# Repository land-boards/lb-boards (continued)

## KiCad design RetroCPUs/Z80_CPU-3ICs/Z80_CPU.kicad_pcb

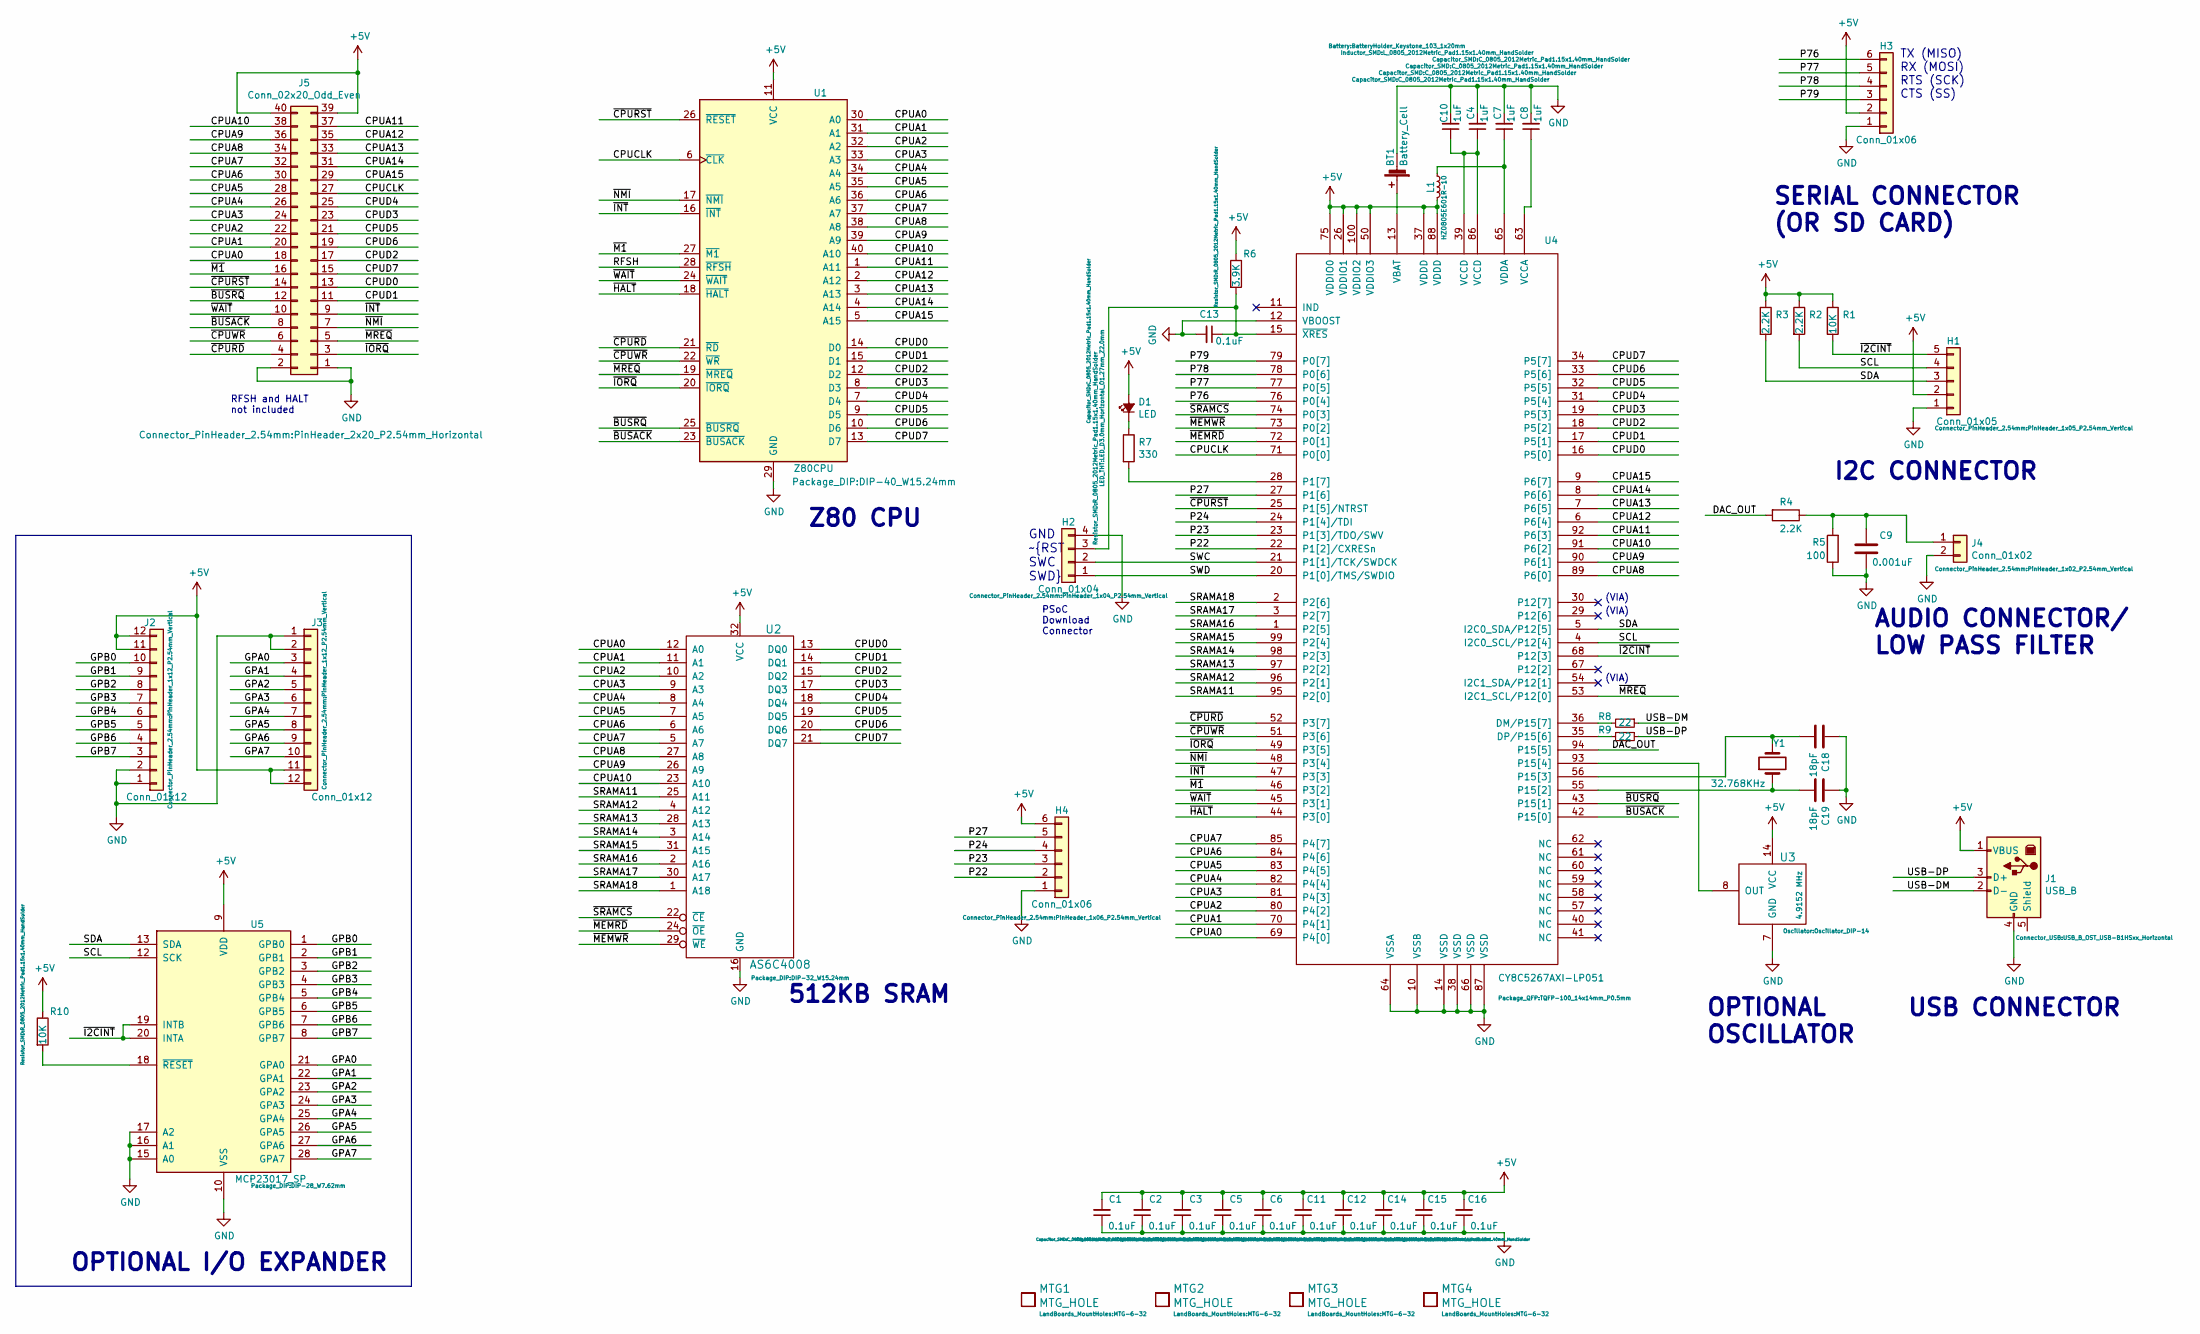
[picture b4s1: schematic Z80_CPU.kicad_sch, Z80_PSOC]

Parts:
BT1: Battery_Cell; BatteryHolder_Keystone_103_1x20mm
C1, C2, C3, C5, C6, C11, C12, C13, C14, C15, C16: 0.1uF; C_0805_2012Metric_Pad1.15x1.40mm_HandSolder
C4, C7, C8, C10: 1uF; C_0805_2012Metric_Pad1.15x1.40mm_HandSolder
C9: 0.001uF; C_0805_2012Metric_Pad1.15x1.40mm_HandSolder
C18, C19: 18pF; C_0805_2012Metric_Pad1.15x1.40mm_HandSolder
D1: LED; LED_D3.0mm_Horizontal_O1.27mm_Z2.0mm
H1: Conn_01x05; PinHeader_1x05_P2.54mm_Vertical
H2: Conn_01x04; PinHeader_1x04_P2.54mm_Vertical
H3, H4: Conn_01x06; PinHeader_1x06_P2.54mm_Vertical
J1: USB_B; USB_B_OST_USB-B1HSxx_Horizontal
J2, J3: Conn_01x12; PinHeader_1x12_P2.54mm_Vertical
J4: Conn_01x02; PinHeader_1x02_P2.54mm_Vertical
J5: Conn_02x20_Odd_Even; PinHeader_2x20_P2.54mm_Horizontal
L1: HZ0805E601R-10; L_0805_2012Metric_Pad1.15x1.40mm_HandSolder
MTG1, MTG2, MTG3, MTG4: MTG_HOLE; MTG-6-32
R1, R10: 10K; R_0805_2012Metric_Pad1.15x1.40mm_HandSolder
R2, R3, R4: 2.2K; R_0805_2012Metric_Pad1.15x1.40mm_HandSolder
R5: 100; R_0805_2012Metric_Pad1.15x1.40mm_HandSolder
R6: 3.9K; R_0805_2012Metric_Pad1.15x1.40mm_HandSolder
R7: 330; R_0805_2012Metric_Pad1.15x1.40mm_HandSolder
R8, R9: 22; R_0805_2012Metric_Pad1.15x1.40mm_HandSolder
U1: Z80CPU; DIP-40_W15.24mm
U2: AS6C4008; DIP-32_W15.24mm
U3: 4.9152 MHz; Oscillator_DIP-14
U4: CY8C5267AXI-LP051; TQFP-100_14x14mm_P0.5mm
U5: MCP23017_SP; DIP-28_W7.62mm
Y1: 32.768KHz; Crystal_C26-LF_D2.1mm_L6.5mm_Horizontal

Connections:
+5V: C1.2, C2.2, C3.2, C5.2, C6.2, C11.2, C12.2, C14.2, C15.2, C16.2, D1.2 (A), H1.2, H3.2, H4.6, J1.1 (VBUS), J2.11, J2.12, J3.11, J3.12, J5.39, J5.40, L1.2, R1.1, R2.1, R3.1, R6.1, R10.1, U1.11 (VCC), U2.32 (VCC), U3.14 (VCC), U4.26 (VDDIO1), U4.37 (VDDD), U4.50 (VDDIO3), U4.75 (VDDIO0), U4.88 (VDDD), U4.100 (VDDIO2), U5.9 (VDD)
/CPUA0: J5.18, U1.30 (A0), U2.12 (A0), U4.69 (P4[0])
/CPUA1: J5.20, U1.31 (A1), U2.11 (A1), U4.70 (P4[1])
/CPUA2: J5.22, U1.32 (A2), U2.10 (A2), U4.80 (P4[2])
/CPUA3: J5.24, U1.33 (A3), U2.9 (A3), U4.81 (P4[3])
/CPUA4: J5.26, U1.34 (A4), U2.8 (A4), U4.82 (P4[4])
/CPUA5: J5.28, U1.35 (A5), U2.7 (A5), U4.83 (P4[5])
/CPUA6: J5.30, U1.36 (A6), U2.6 (A6), U4.84 (P4[6])
/CPUA7: J5.32, U1.37 (A7), U2.5 (A7), U4.85 (P4[7])
/CPUA8: J5.34, U1.38 (A8), U2.27 (A8), U4.89 (P6[0])
/CPUA9: J5.36, U1.39 (A9), U2.26 (A9), U4.90 (P6[1])
/CPUA10: J5.38, U1.40 (A10), U2.23 (A10), U4.91 (P6[2])
/CPUA11: J5.37, U1.1 (A11), U4.92 (P6[3])
/CPUA12: J5.35, U1.2 (A12), U4.6 (P6[4])
/CPUA13: J5.33, U1.3 (A13), U4.7 (P6[5])
/CPUA14: J5.31, U1.4 (A14), U4.8 (P6[6])
/CPUA15: J5.29, U1.5 (A15), U4.9 (P6[7])
/CPUCLK: J5.27, U1.6 (~CLK), U4.71 (P0[0])
/CPUD0: J5.13, U1.14 (D0), U2.13 (DQ0), U4.16 (P5[0])
/CPUD1: J5.11, U1.15 (D1), U2.14 (DQ1), U4.17 (P5[1])
/CPUD2: J5.17, U1.12 (D2), U2.15 (DQ2), U4.18 (P5[2])
/CPUD3: J5.23, U1.8 (D3), U2.17 (DQ3), U4.19 (P5[3])
/CPUD4: J5.25, U1.7 (D4), U2.18 (DQ4), U4.31 (P5[4])
/CPUD5: J5.21, U1.9 (D5), U2.19 (DQ5), U4.32 (P5[5])
/CPUD6: J5.19, U1.10 (D6), U2.20 (DQ6), U4.33 (P5[6])
/CPUD7: J5.15, U1.13 (D7), U2.21 (DQ7), U4.34 (P5[7])
/DAC_OUT: R4.2, U4.94 (P15[5])
/GPA0: J3.3, U5.21 (GPA0)
/GPA1: J3.4, U5.22 (GPA1)
/GPA2: J3.5, U5.23 (GPA2)
/GPA3: J3.6, U5.24 (GPA3)
/GPA4: J3.7, U5.25 (GPA4)
/GPA5: J3.8, U5.26 (GPA5)
/GPA6: J3.9, U5.27 (GPA6)
/GPA7: J3.10, U5.28 (GPA7)
/GPB0: J2.10, U5.1 (GPB0)
/GPB1: J2.9, U5.2 (GPB1)
/GPB2: J2.8, U5.3 (GPB2)
/GPB3: J2.7, U5.4 (GPB3)
/GPB4: J2.6, U5.5 (GPB4)
/GPB5: J2.5, U5.6 (GPB5)
/GPB6: J2.4, U5.7 (GPB6)
/GPB7: J2.3, U5.8 (GPB7)
/P22: H4.2, U4.22 (P1[2]/CXRESn)
/P23: H4.3, U4.23 (P1[3]/TDO/SWV)
/P24: H4.4, U4.24 (P1[4]/TDI)
/P27: H4.5, U4.27 (P1[6])
/P76: H3.6, U4.76 (P0[4])
/P77: H3.5, U4.77 (P0[5])
/P78: H3.4, U4.78 (P0[6])
/P79: H3.3, U4.79 (P0[7])
/SCL: H1.4, R2.2, U4.4 (I2C0_SCL/P12[4]), U5.12 (SCK)
/SDA: H1.3, R3.2, U4.5 (I2C0_SDA/P12[5]), U5.13 (SDA)
/SRAMA11: U2.25 (A11), U4.95 (P2[0])
/SRAMA12: U2.4 (A12), U4.96 (P2[1])
/SRAMA13: U2.28 (A13), U4.97 (P2[2])
/SRAMA14: U2.3 (A14), U4.98 (P2[3])
/SRAMA15: U2.31 (A15), U4.99 (P2[4])
/SRAMA16: U2.2 (A16), U4.1 (P2[5])
/SRAMA17: U2.30 (A17), U4.3 (P2[7])
/SRAMA18: U2.1 (A18), U4.2 (P2[6])
/SWC: H2.2, U4.21 (P1[1]/TCK/SWDCK)
/SWD: H2.1, U4.20 (P1[0]/TMS/SWDIO)
/USB-DM: J1.2 (D-), R8.1
/USB-DP: J1.3 (D+), R9.1
/~BUSACK: J5.8, U1.23 (~BUSACK), U4.42 (P15[0])
/~BUSRQ: J5.12, U1.25 (~BUSRQ), U4.43 (P15[1])
/~CPURD: J5.4, U1.21 (~RD), U4.52 (P3[7])
/~CPURST: J5.14, U1.26 (~RESET), U4.25 (P1[5]/NTRST)
/~CPUWR: J5.6, U1.22 (~WR), U4.51 (P3[6])
/~HALT: U1.18 (~HALT), U4.44 (P3[0])
/~I2CINT: H1.5, R1.2, U4.68 (P12[3]), U5.19 (INTB), U5.20 (INTA)
/~INT: J5.9, U1.16 (~INT), U4.47 (P3[3])
/~IORQ: J5.3, U1.20 (~IORQ), U4.49 (P3[5])
/~M1: J5.16, U1.27 (~M1), U4.46 (P3[2])
/~MEMRD: U2.24 (~OE), U4.72 (P0[1])
/~MEMWR: U2.29 (~WE), U4.73 (P0[2])
/~MREQ: J5.5, U1.19 (~MREQ), U4.53 (I2C1_SCL/P12[0])
/~NMI: J5.7, U1.17 (~NMI), U4.48 (P3[4])
/~SRAMCS: U2.22 (~CE), U4.74 (P0[3])
/~WAIT: J5.10, U1.24 (~WAIT), U4.45 (P3[1])
GND: BT1.2 (-), C1.1, C2.1, C3.1, C4.2, C5.1, C6.1, C7.2, C8.2, C9.1, C10.2, C11.1, C12.1, C13.2, C14.1, C15.1, C16.1, C18.1, C19.1, H1.1, H2.4, H3.1, H4.1, J1.4 (GND), J2.1, J2.2, J3.1, J3.2, J4.2, J5.1, J5.2, R5.1, U1.29 (GND), U2.16 (GND), U3.7 (GND), U4.10 (VSSB), U4.12 (VBOOST), U4.14 (VSSD), U4.38 (VSSD), U4.64 (VSSA), U4.66 (VSSD), U4.87 (VSSD), U5.10 (VSS), U5.15 (A0), U5.16 (A1), U5.17 (A2)
unnamed: BT1.1 (+), U4.13 (VBAT)
unnamed: C7.1, L1.1, U4.65 (VDDA)
unnamed: C8.1, U4.63 (VCCA)
unnamed: C9.2, J4.1, R4.1, R5.2
unnamed: C4.1, C10.1, U4.39 (VCCD), U4.86 (VCCD)
unnamed: C13.1, H2.3, R6.2, U4.15 (~XRES)
unnamed: C18.2, U4.56 (P15[3]), Y1.2
unnamed: C19.2, U4.55 (P15[2]), Y1.1
unnamed: D1.1 (K), R7.1
unnamed: R7.2, U4.28 (P1[7])
unnamed: R8.2, U4.36 (DM/P15[7])
unnamed: R9.2, U4.35 (DP/P15[6])
unnamed: R10.2, U5.18 (~RESET)
unnamed: U3.8 (OUT), U4.93 (P15[4])

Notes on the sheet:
Z80 CPU
OPTIONAL I/O EXPANDER
(VIA)
OPTIONAL OSCILLATOR
AUDIO CONNECTOR/ LOW PASS FILTER
I2C CONNECTOR
SERIAL CONNECTOR (OR SD CARD)
USB CONNECTOR
512KB SRAM
PSoC Download Connector
TX (MISO) RX (MOSI) RTS (SCK) CTS (SS)
GND ~{RST SWC SWD}
RFSH and HALT not included

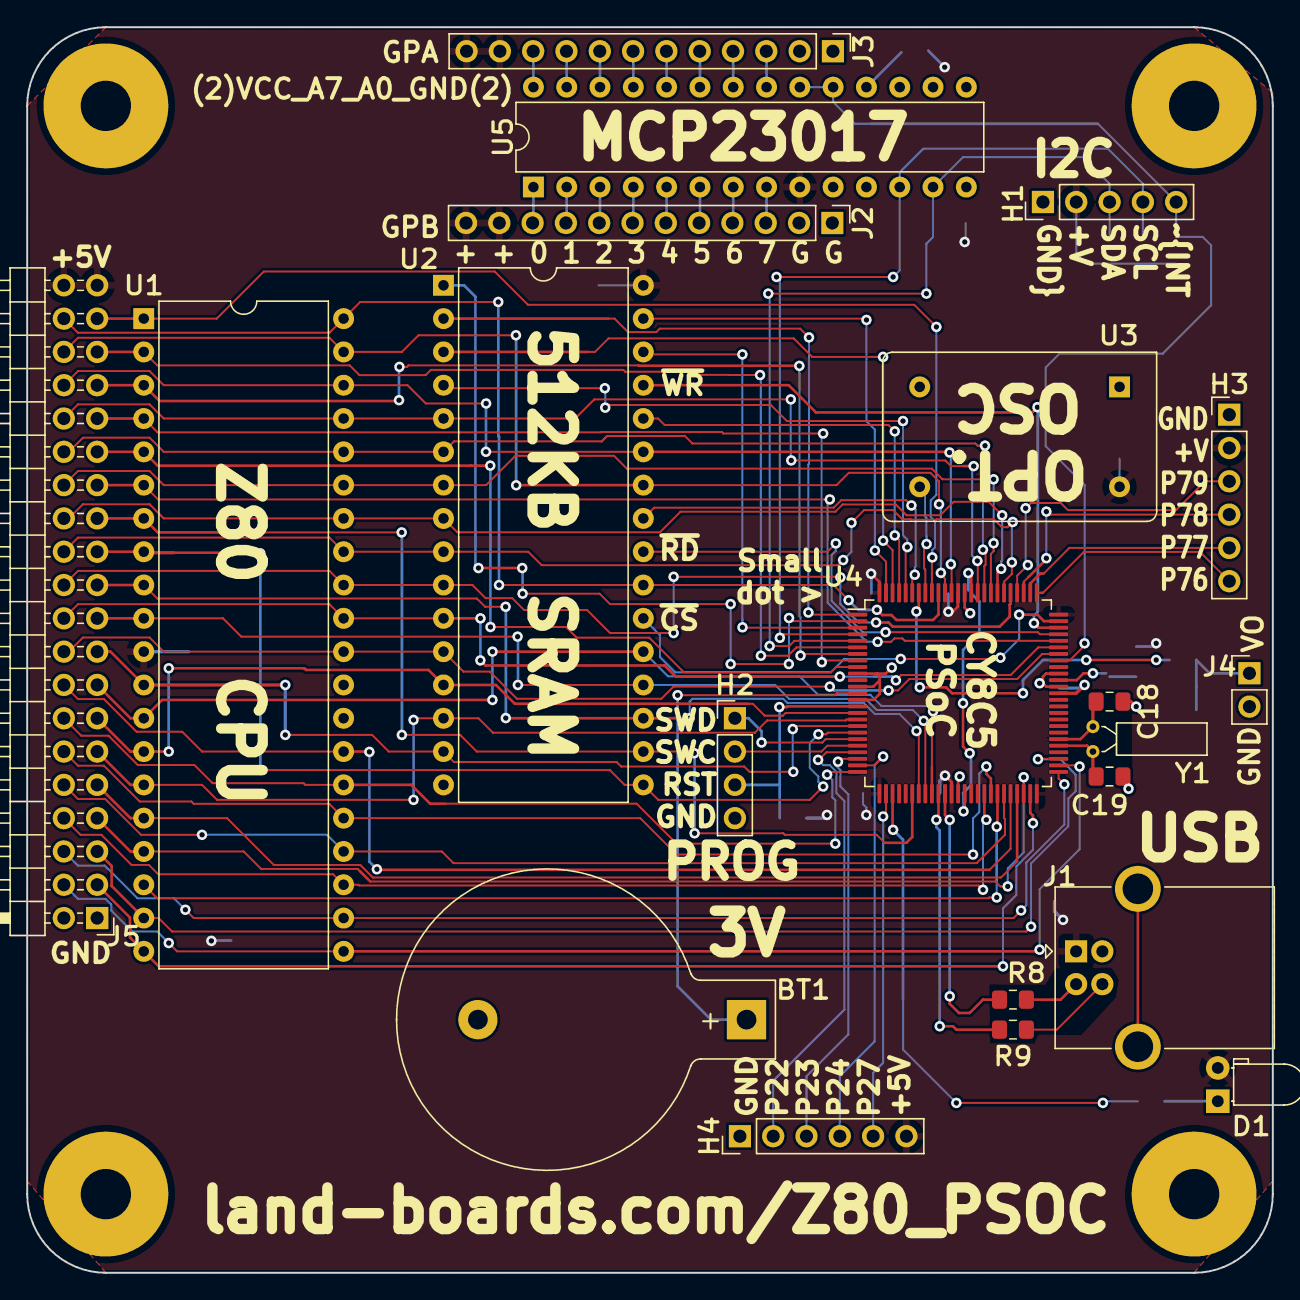
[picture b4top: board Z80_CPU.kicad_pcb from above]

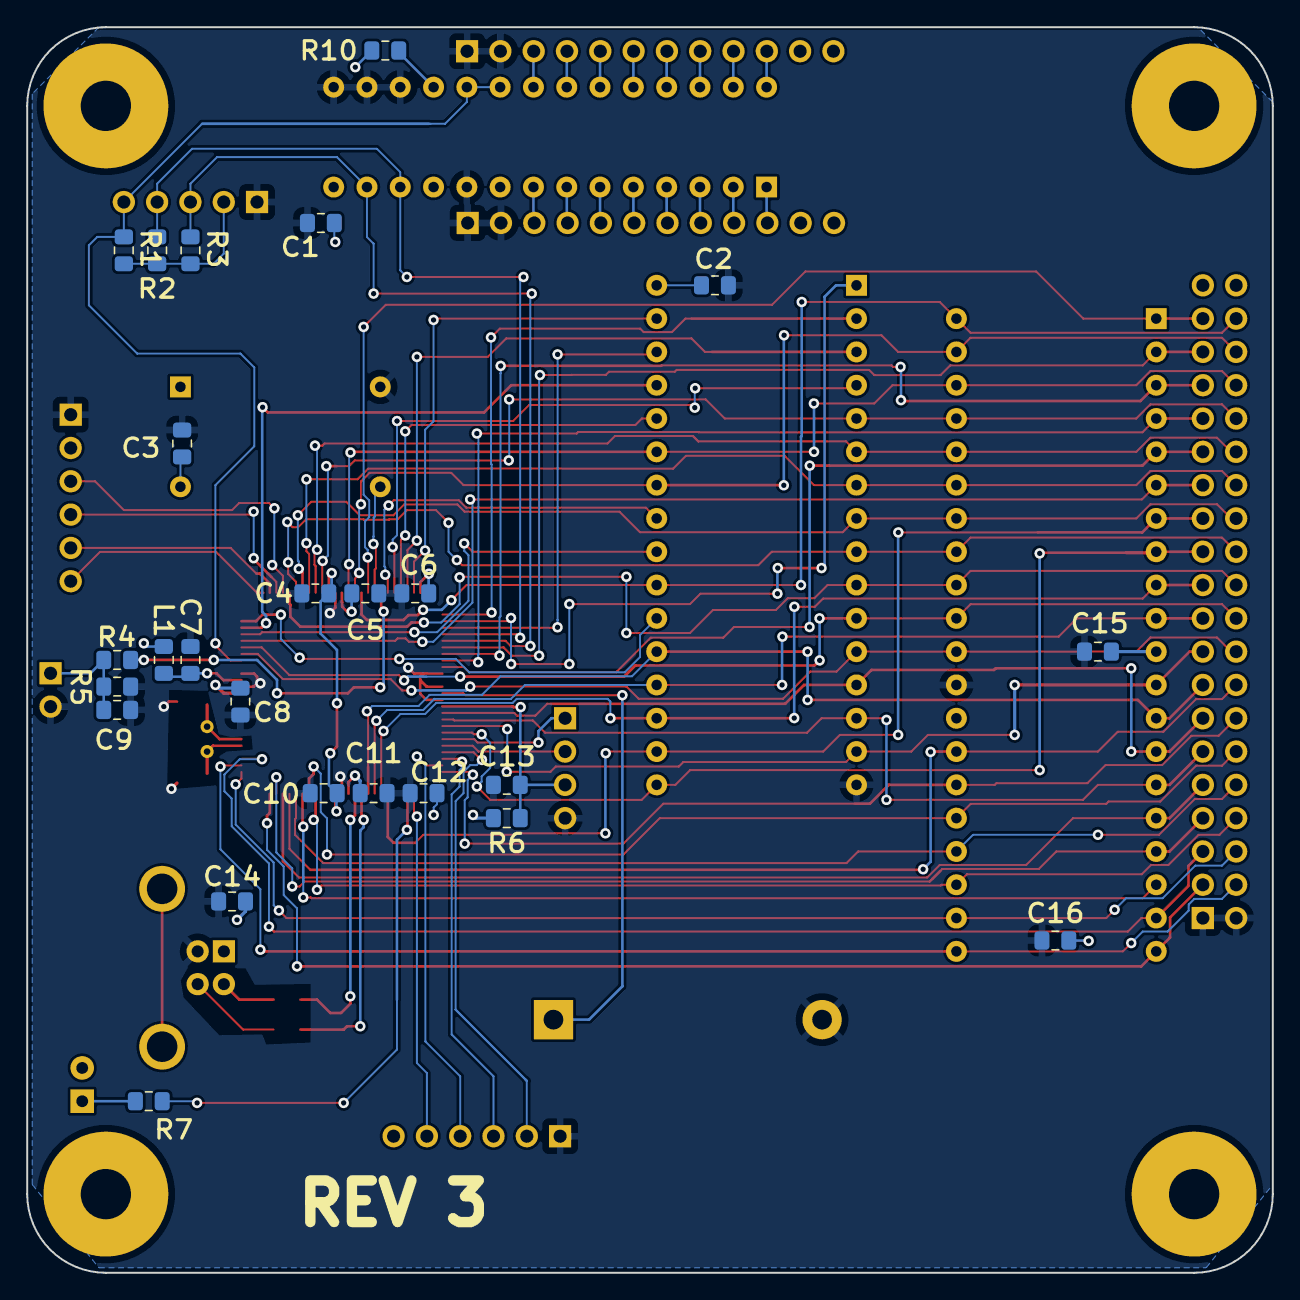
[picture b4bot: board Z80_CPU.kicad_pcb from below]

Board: 2 copper layers, 95.0 x 95.0 mm, 50 parts (25 on the bottom side), 96 nets.

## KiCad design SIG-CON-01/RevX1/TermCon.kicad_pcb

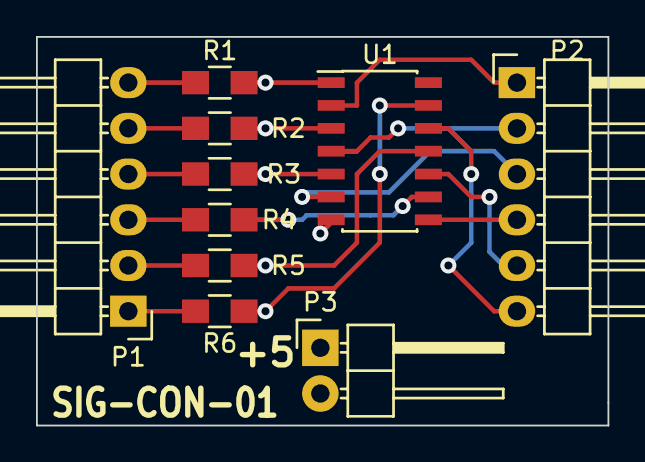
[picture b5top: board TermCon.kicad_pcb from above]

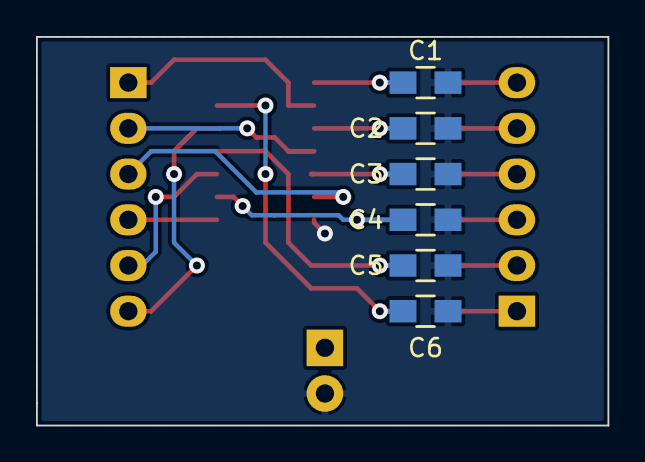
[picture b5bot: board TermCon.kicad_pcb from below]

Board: 2 copper layers, 31.8 x 21.6 mm, 16 parts (6 on the bottom side), 19 nets.

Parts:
C1, C2, C3, C4, C5, C6: C; C_0805_HandSoldering
P1, P2: CONN_01X06; Pin_Header_Angled_1x06
P3: CONN_01X02; Pin_Header_Angled_1x02
R1, R2, R3, R4, R5, R6: R; R_0805_HandSoldering
U1: 74AC14; SOIC-14_3.9x8.7mm_Pitch1.27mm

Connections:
GND: C1.2, C2.2, C3.2, C4.2, C5.2, C6.2, P3.2, U1.7
unnamed: C1.1, R1.1, U1.1
unnamed: C2.1, R2.1, U1.3
unnamed: C3.1, R3.1, U1.5
unnamed: C4.1, R4.1, U1.9
unnamed: C5.1, R5.1, U1.11
unnamed: C6.1, R6.1, U1.13
unnamed: P1.1, R6.2
unnamed: P1.2, R5.2
unnamed: P1.3, R4.2
unnamed: P1.4, R3.2
unnamed: P1.5, R2.2
unnamed: P1.6, R1.2
unnamed: P2.1, U1.2
unnamed: P2.2, U1.4
unnamed: P2.3, U1.6
unnamed: P2.4, U1.8
unnamed: P2.5, U1.10
unnamed: P2.6, U1.12

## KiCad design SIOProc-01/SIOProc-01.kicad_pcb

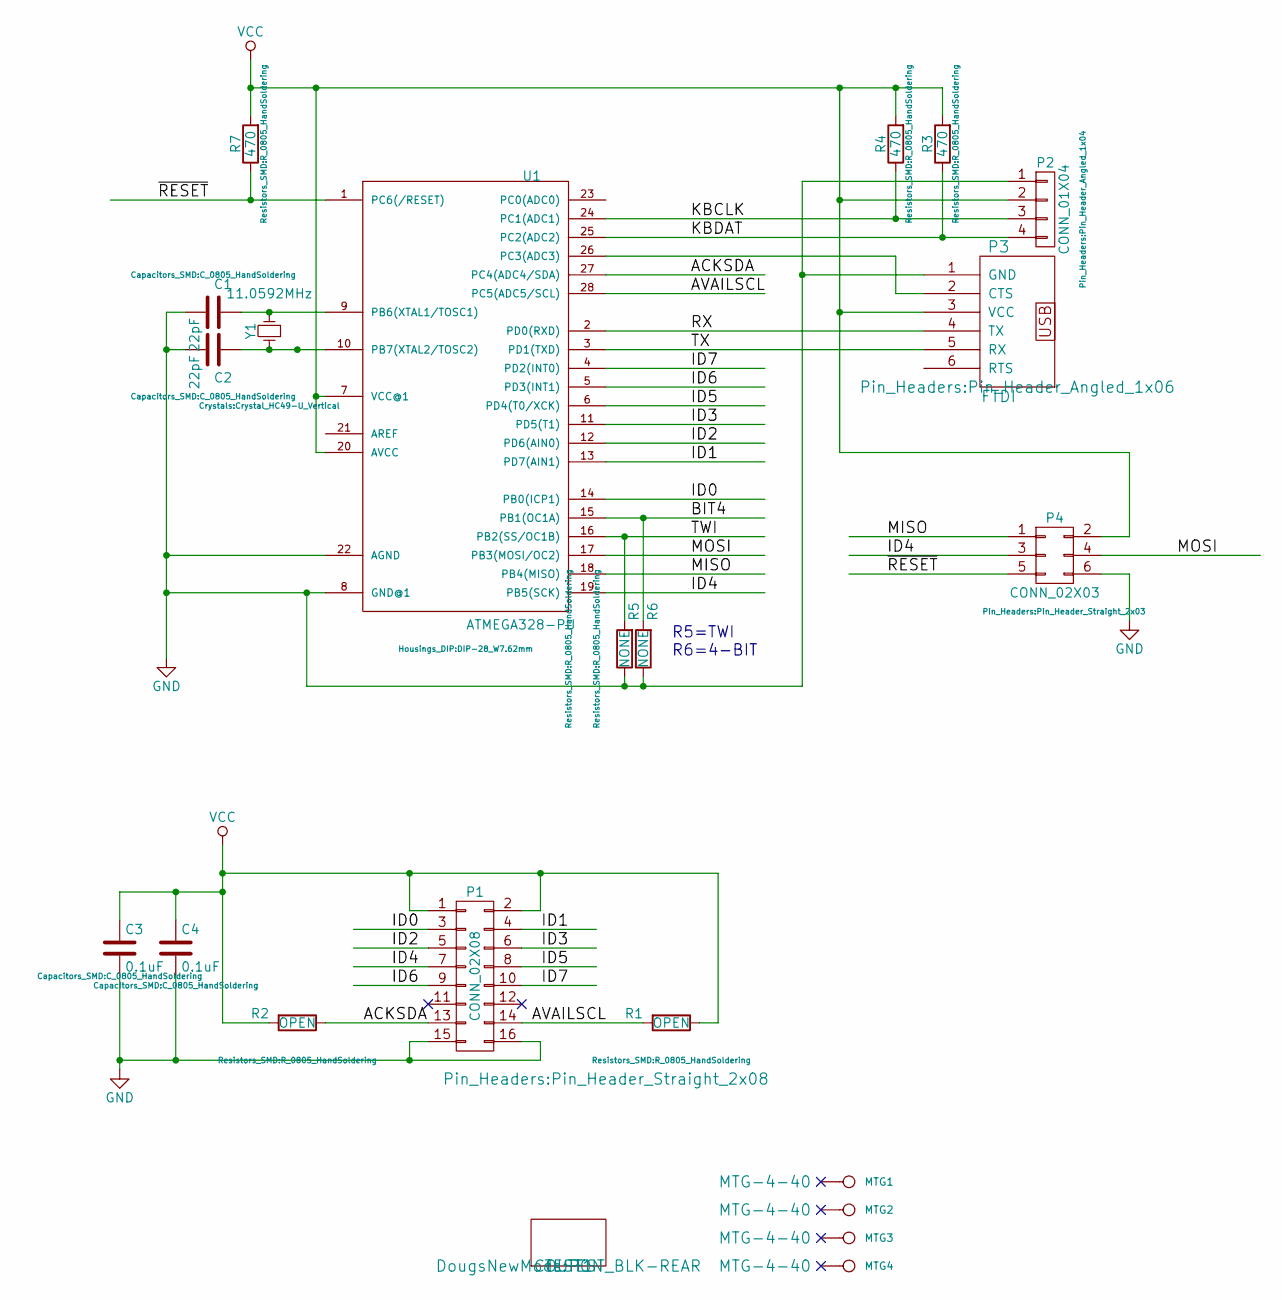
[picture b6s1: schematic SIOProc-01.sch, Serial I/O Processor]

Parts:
C1, C2: 22pF; C_0805_HandSoldering
C3, C4: 0.1uF; C_0805_HandSoldering
MTG1, MTG2, MTG3, MTG4: CONN_1; MTG-4-40
P1: CONN_02X08; Pin_Header_Straight_2x08
P2: CONN_01X04; Pin_Header_Angled_1x04
P3: FTDI; Pin_Header_Angled_1x06
P4: CONN_02X03; Pin_Header_Straight_2x03
R1, R2: OPEN; R_0805_HandSoldering
R3, R4, R7: 470; R_0805_HandSoldering
R5, R6: NONE; R_0805_HandSoldering
TEST1: COUPON; TEST_BLK-REAR
U1: ATMEGA328-PU; DIP-28_W7.62mm
Y1: 11.0592MHz; Crystal_HC49-U_Vertical

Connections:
/ACKSDA: P1.13, R2.1, U1.27 (PC4(ADC4/SDA))
/AVAILSCL: P1.14, R1.2, U1.28 (PC5(ADC5/SCL))
/BIT4: R6.2, U1.15 (PB1(OC1A))
/ID0: P1.3, U1.14 (PB0(ICP1))
/ID1: P1.4, U1.13 (PD7(AIN1))
/ID2: P1.5, U1.12 (PD6(AIN0))
/ID3: P1.6, U1.11 (PD5(T1))
/ID4: P1.7, P4.3, U1.19 (PB5(SCK))
/ID5: P1.8, U1.6 (PD4(T0/XCK))
/ID6: P1.9, U1.5 (PD3(INT1))
/ID7: P1.10, U1.4 (PD2(INT0))
/KBCLK: P2.3, R4.1, U1.24 (PC1(ADC1))
/KBDAT: P2.4, R3.1, U1.25 (PC2(ADC2))
/MISO: P4.1, U1.18 (PB4(MISO))
/MOSI: P4.4, U1.17 (PB3(MOSI/OC2))
/RX: P3.4 (TX), U1.2 (PD0(RXD))
/TWI: R5.2, U1.16 (PB2(SS/OC1B))
/TX: P3.5 (RX), U1.3 (PD1(TXD))
/~RESET: P4.5, R7.1, U1.1 (PC6(/RESET))
GND: C1.2, C2.2, C3.2, C4.2, P1.15, P1.16, P2.1, P3.1 (GND), P4.6, R5.1, R6.1, U1.8 (GND@1), U1.22 (AGND)
unnamed: C1.1, U1.9 (PB6(XTAL1/TOSC1)), Y1.2
unnamed: C2.1, U1.10 (PB7(XTAL2/TOSC2)), Y1.1
VCC: C3.1, C4.1, P1.1, P1.2, P2.2, P3.3 (VCC), P4.2, R1.1, R2.2, R3.2, R4.2, R7.2, U1.7 (VCC@1), U1.20 (AVCC)

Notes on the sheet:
R5=TWI R6=4-BIT

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
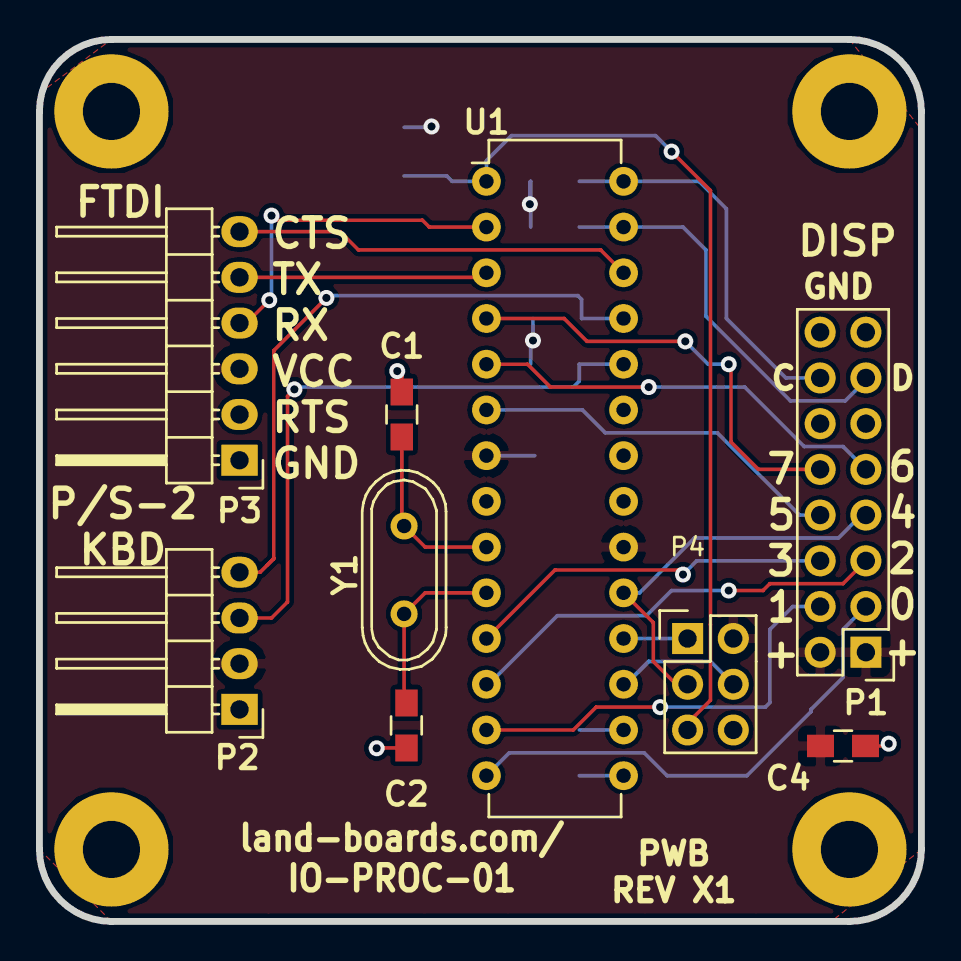
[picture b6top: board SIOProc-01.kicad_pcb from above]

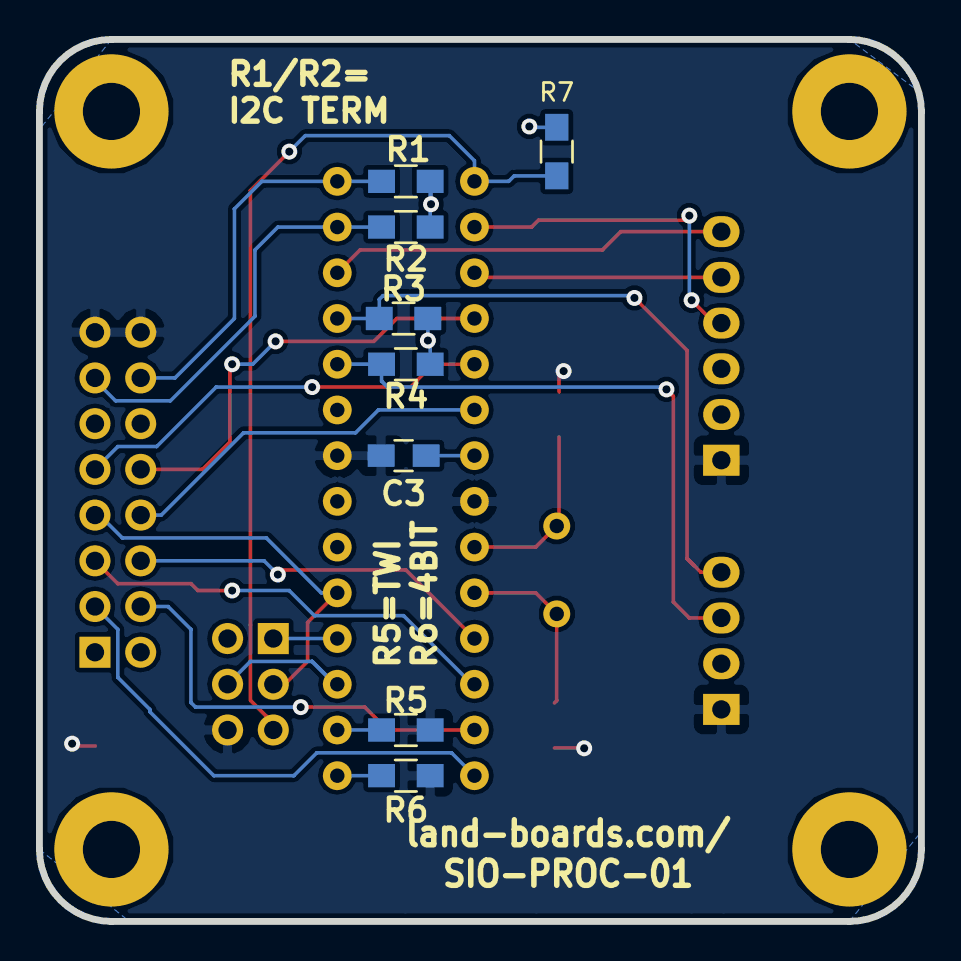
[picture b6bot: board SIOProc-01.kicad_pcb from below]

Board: 2 copper layers, 49.0 x 49.0 mm, 21 parts (8 on the bottom side), 24 nets.

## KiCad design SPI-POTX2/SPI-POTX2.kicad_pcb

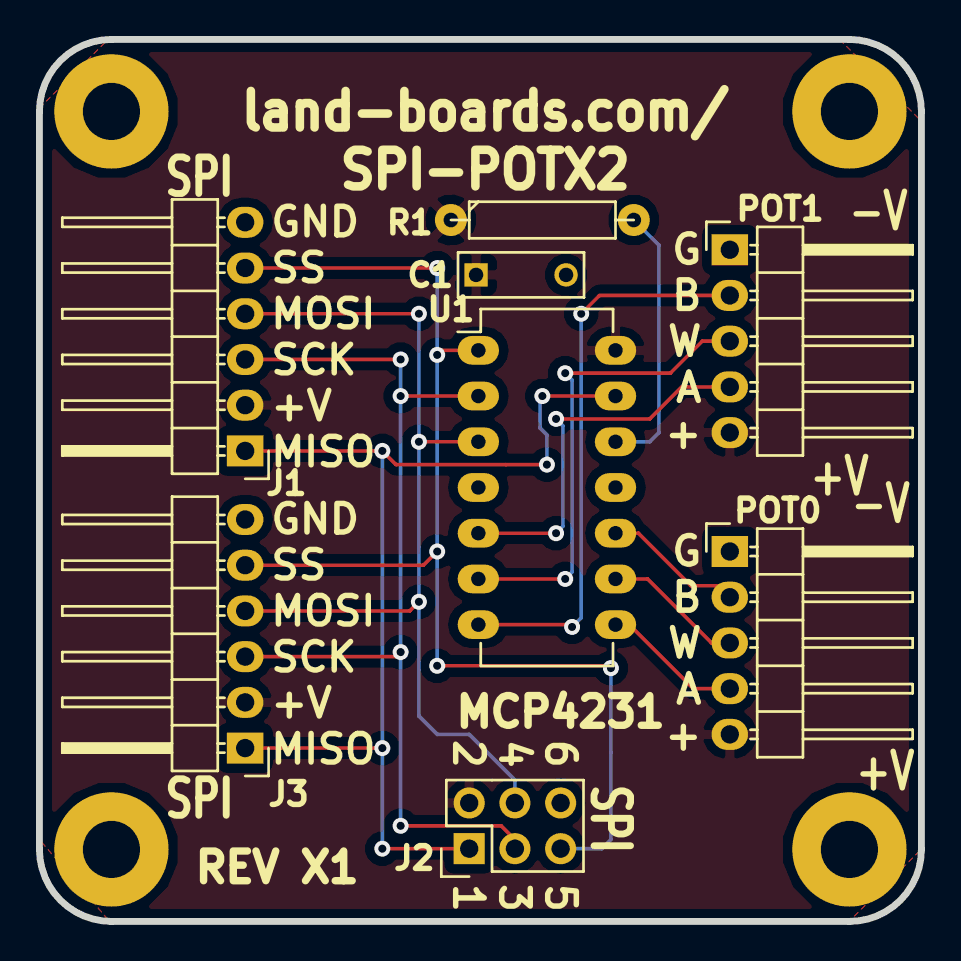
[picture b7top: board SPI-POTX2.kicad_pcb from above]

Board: 2 copper layers, 49.0 x 49.0 mm, 13 parts (0 on the bottom side), 13 nets.

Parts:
C1: 0.1uF; C_Rect_L7_W2.5_P5
J1, J3: CONN_01X06; Pin_Header_Angled_1x06
J2: CONN_02X03; Pin_Header_Straight_2x03
MTG5, MTG6, MTG7: MTG_HOLE; MTG-4-40
MTG?1: MTG_HOLE; MTG-4-40
POT0, POT1: CONN_01X05; Pin_Header_Angled_1x05
R1: 10K; R4-LARGE_PADS
TEST: TEST; TEST_BLK-REAR
U1: MCP4231-103E/P; DIP-14_W7.62mm_LongPads

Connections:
/MISO: J1.1, J2.1, J3.1, U1.13
/MOSI: J1.4, J2.4, J3.4, U1.3
/P0A: POT0.4, U1.8
/P0B: POT0.2, U1.10
/P0W: POT0.3, U1.9
/P1A: POT1.4, U1.5
/P1B: POT1.2, U1.7
/P1W: POT1.3, U1.6
/SCK: J1.3, J2.3, J3.3, U1.2
/SS: J1.5, J2.5, J3.5, U1.1
/VCC: C1.1, J1.2, J2.2, J3.2, POT0.5, POT1.5, R1.1, U1.14
GND: C1.2, J1.6, J2.6, J3.6, POT0.1, POT1.1, U1.4
unnamed: R1.2, U1.12

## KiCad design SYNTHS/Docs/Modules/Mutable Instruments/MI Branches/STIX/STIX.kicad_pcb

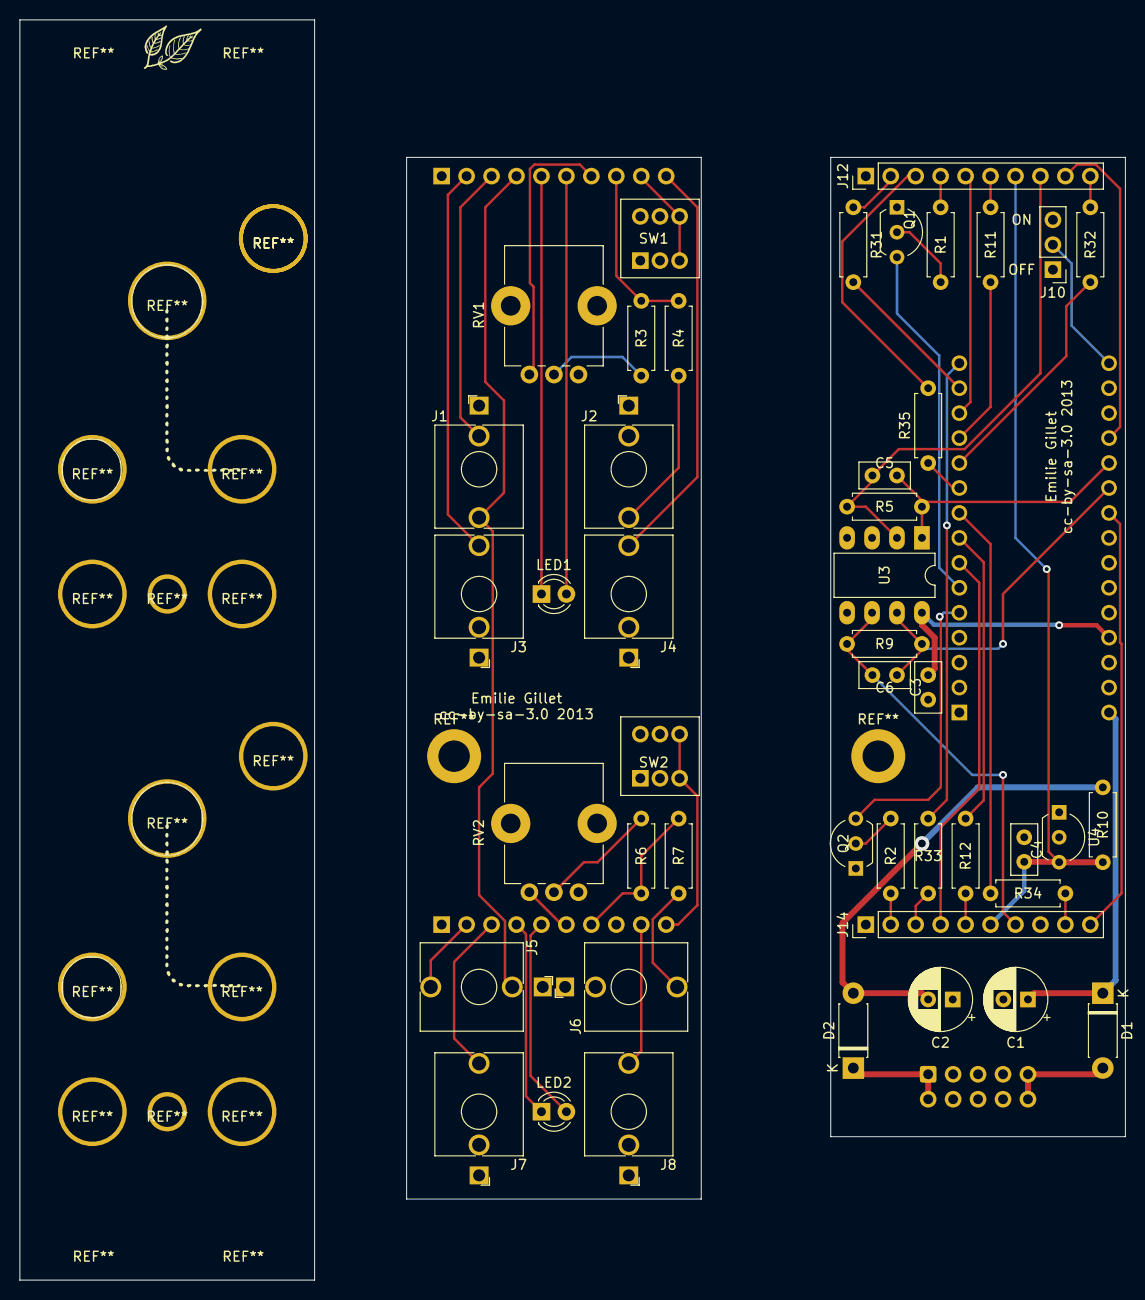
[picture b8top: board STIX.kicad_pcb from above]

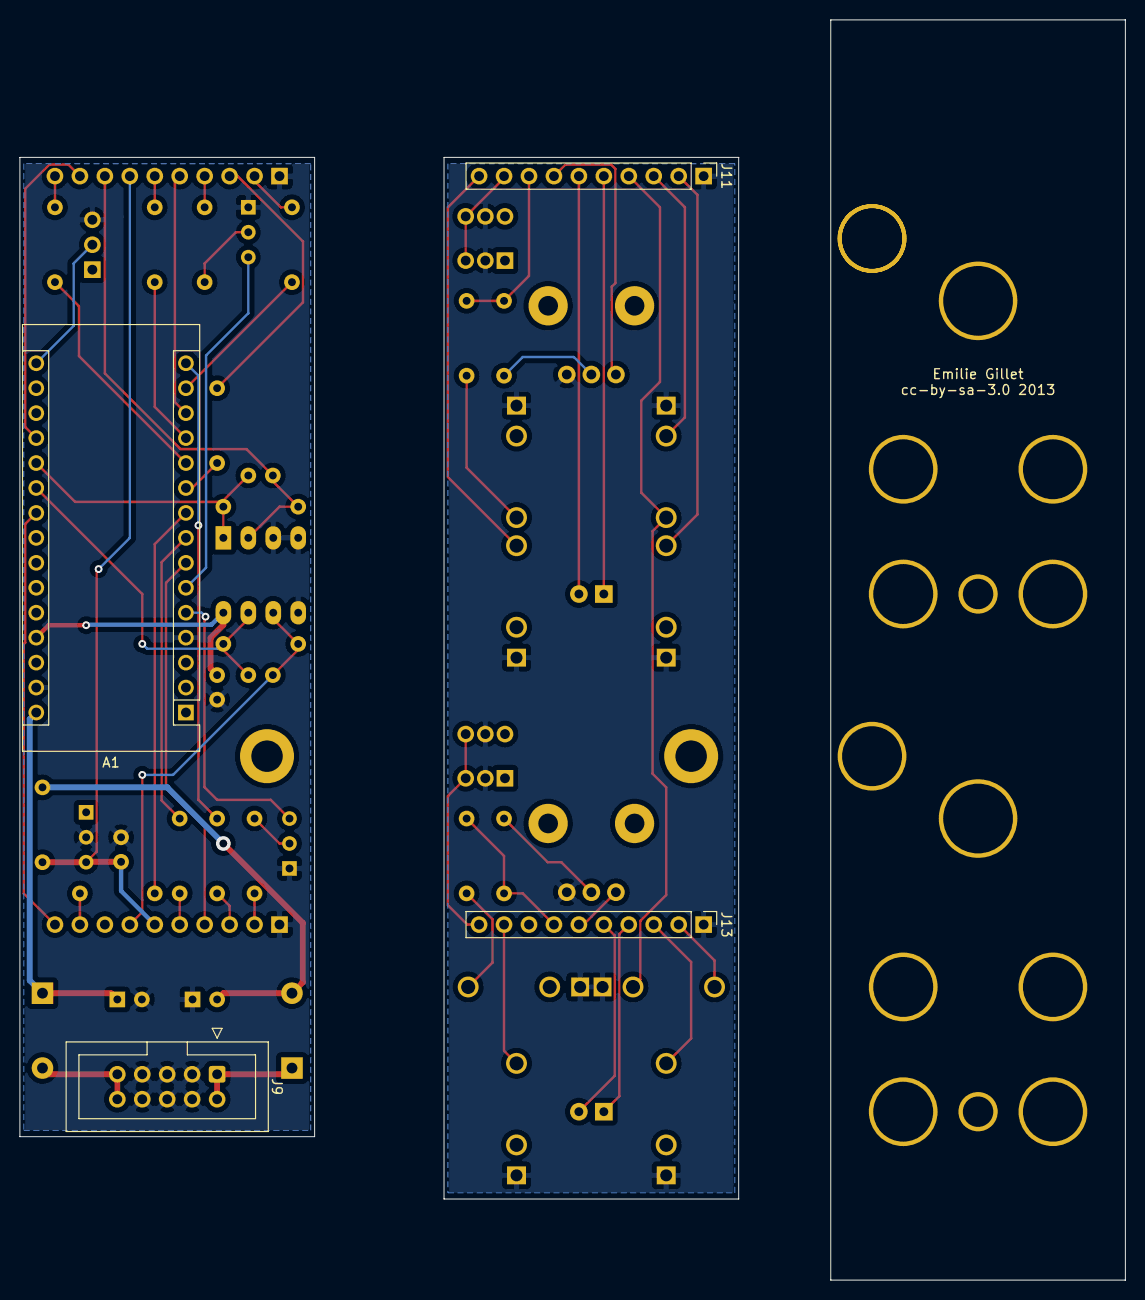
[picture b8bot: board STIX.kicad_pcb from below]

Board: 2 copper layers, 112.6 x 128.3 mm, 49 parts (4 on the bottom side), 40 nets.

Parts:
A1: Arduino_Nano_v3.x; Arduino_Nano
C1, C2: 10uF; CP_Radial_D6.3mm_P2.50mm
C3, C4: 100n; C_Disc_D5.0mm_W2.5mm_P2.50mm
C5, C6: 1n; C_Disc_D5.0mm_W2.5mm_P2.50mm
D1, D2: 1N4001; D_DO-41_SOD81_P7.62mm_Horizontal
J1, J2, J3, J4, J5, J6, J7, J8: Jack; ModdedThonkiconn
J9: Conn_02x05_Odd_Even; IDC-Header_2x05_P2.54mm_Vertical
J10: Conn_3; PinHeader_1x03_P2.54mm_Vertical
J11, J13: Conn_01x10_Male; PinHeader_1x10_P2.54mm_Vertical
J12, J14: Conn_01x10_Female; PinHeader_1x10_P2.54mm_Vertical
LED1, LED2: LED_Dual_2pin; LED_D3.0mm
Q1, Q2: 2N3904; TO-92L_Inline_Wide
R1, R2, R3, R4, R5, R6, R7, R9: 100K; R_Axial_DIN0207_L6.3mm_D2.5mm_P7.62mm_Horizontal
R10: 5.1k; R_Axial_DIN0207_L6.3mm_D2.5mm_P7.62mm_Horizontal
R11, R12: 220; R_Axial_DIN0207_L6.3mm_D2.5mm_P7.62mm_Horizontal
R31, R32, R33, R34, R35: 1K; R_Axial_DIN0207_L6.3mm_D2.5mm_P7.62mm_Horizontal
RV1, RV2: R_POT; ModdedPotentiometer
SW1, SW2: SW_Push_DPDT; DPDT_Momentary_Push_Button_Switch
U3: MCP6002-xP; DIP-8_W7.62mm_LongPads
U4: LM4040LP-5; TO-92L_Inline_Wide

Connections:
+5V: A1.27, C3.2, U3.8
+12V: A1.30, C1.1, D1.1
-5V: C4.2, J11.7, J12.7, J13.6, J14.6, R10.2, RV1.3, RV2.3, U4.3
-12V: C2.2, D2.2, R10.1
AUTONOISE: A1.16, J10.2
GND: A1.4, A1.29, C1.2, C2.1, C3.1, C4.1, J1.S, J2.S, J3.S, J4.S, J5.S, J6.S, J7.S, J8.S, J9.3, J9.4, J9.5, J9.6, J9.7, J9.8, J10.3, J11.1, J12.1, J13.1, J14.1, Q1.1, Q2.1, RV1.1, RV2.1, SW1.2, SW1.5, SW2.2, SW2.5, U3.3, U3.4, U3.5, U4.2
IN1: A1.6, Q1.3
IN2: A1.5, Q2.3
LED1A: A1.13, J11.5, J12.5, LED1.1
LED1B: A1.12, R11.1
LED2A: A1.7, J13.4, J14.4, LED2.1
LED2B: A1.8, R12.1
NORM: A1.10, R35.1
unnamed: D1.2, J9.9, J9.10
unnamed: D2.1, J9.1, J9.2
unnamed: J2.T, R4.2
unnamed: J6.T, R7.2
unnamed: Q1.2, R1.1
unnamed: Q2.2, R2.1
unnamed: R3.2, RV1.2
unnamed: R6.2, RV2.2
OUT1A: A1.14, R31.2
OUT1B: A1.11, R32.2
OUT2A: A1.15, R33.2
OUT2B: A1.9, R34.2
P1: A1.20, C5.1, R5.1, U3.1
P2: A1.21, C6.1, R9.1, U3.7
SW1: A1.19, J11.9, J12.9, SW1.3, SW1.6
SW2: A1.22, J13.10, J14.10, SW2.3, SW2.6
_IN1: J1.T, J5.TN, J11.4, J12.4, R1.2
_IN2: J5.T, J13.2, J14.2, R2.2
_LED1B: J11.6, J12.6, LED1.2, R11.2
_LED2B: J13.5, J14.5, LED2.2, R12.2
_NORM: J1.TN, J11.3, J12.3, R35.2
_OUT1A: J3.T, J11.2, J12.2, R31.1
_OUT1B: J4.T, J11.10, J12.10, R32.1
_OUT2A: J7.T, J13.3, J14.3, R33.1
_OUT2B: J8.T, J13.9, J14.9, R34.1
_P1: C5.2, J11.8, J12.8, R3.1, R4.1, R5.2, U3.2
_P2: C6.2, J13.7, J14.7, R6.1, R7.1, R9.2, U3.6
